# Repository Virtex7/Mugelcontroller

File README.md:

# Mugelcontroller
kleiner 12V-Umrichter für einen Secop-BD50 Kältekompressor

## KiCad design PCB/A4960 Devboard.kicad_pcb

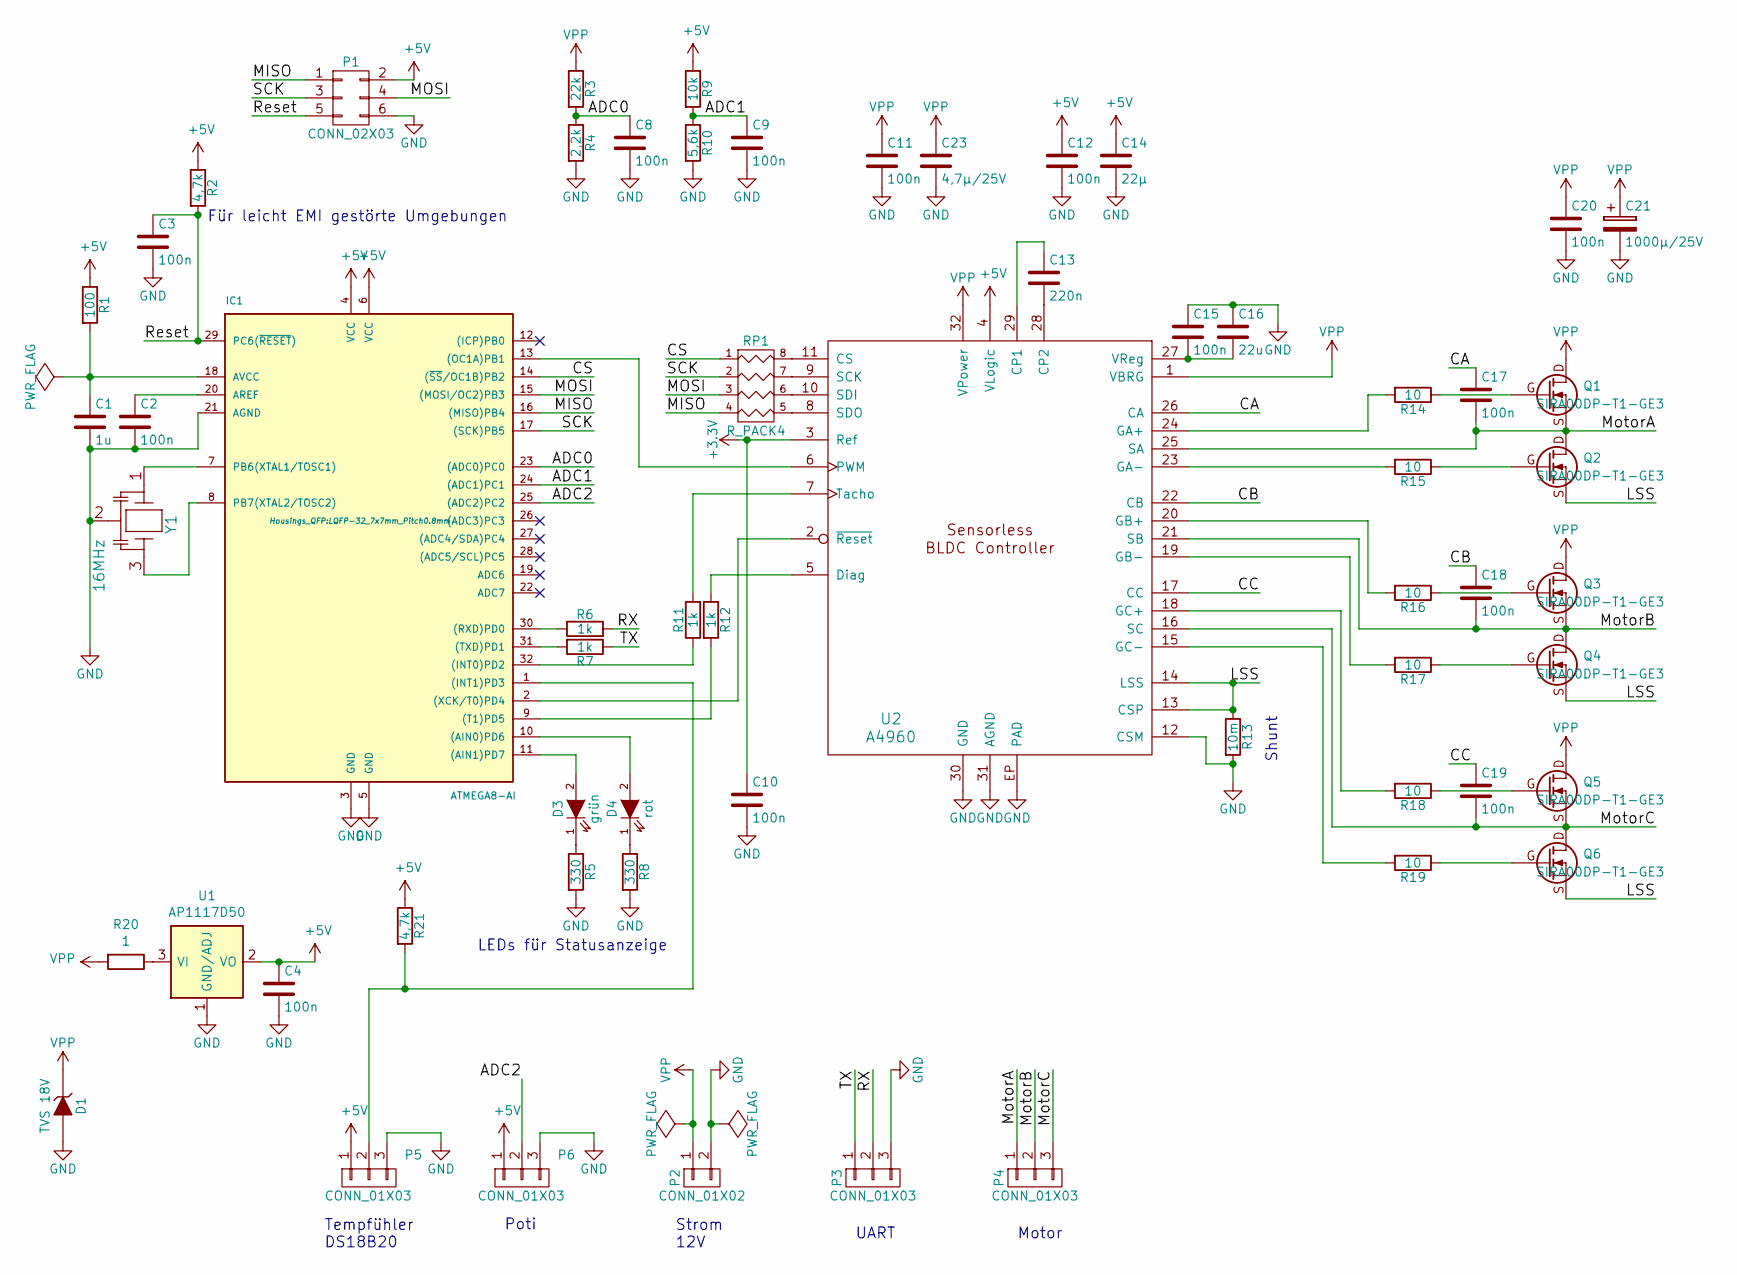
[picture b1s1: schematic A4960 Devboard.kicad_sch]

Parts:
C1: 1u; C_0603
C2, C3, C4, C8, C9, C10, C11, C12, C15, C17, C18, C19, C20: 100n; C_0603
C13: 220n; C_0603
C14: 22µ; C_1206
C16: 22u; C_1206
C21: 1000µ/25V; C_Radial_D8_L11.5_P3.5
C23: 4,7µ/25V; C_1206
D1: TVS 18V; SOD-123
D3: grün; LED-0603
D4: rot; LED-0603
IC1: ATMEGA8-AI; LQFP-32_7x7mm_Pitch0.8mm
P1: CONN_02X03; Pin_Header_Straight_2x03
P2: CONN_01X02; Pin_Header_Straight_1x02
P3, P4, P5, P6: CONN_01X03; Pin_Header_Straight_1x03
Q1, Q2, Q3, Q4, Q5, Q6: SIRA00DP-T1-GE3; SO8_WITH_Heatpipes_New
R1: 100; R_0603
R2, R21: 4,7k; R_0603
R3: 22k; R_0603
R4: 2,2k; R_0603
R5, R8: 330; R_0603
R6, R7, R11, R12: 1k; R_0603
R9: 10k; R_0603
R10: 5,6k; R_0603
R13: 10m; R_2512; Digikey-Nummer RHM.010AUCT-ND
R14, R15, R16, R17, R18, R19: 10; R_0603
R20: 1; R_0805
RP1: R_PACK4; R_Array_Concave_4x0603
U1: AP1117D50; SOT-223
U2: A4960; TQFP-32_7x7mm_Pitch0.8mm; Digikey-Nummer 620-1452-1-ND
Y1: 16MHz; CerOsc_3,2x1,3

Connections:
/ADC0: C8.1, IC1.23 ((ADC0)PC0), R3.2, R4.1
/ADC1: C9.1, IC1.24 ((ADC1)PC1), R9.2, R10.1
/CA: C17.1, U2.26 (CA)
/CB: C18.1, U2.22 (CB)
/CC: C19.1, U2.17 (CC)
/CS: IC1.14 ((~SS~/OC1B)PB2), RP1.1
/LSS: Q2.S, Q4.S, Q6.S, R13.1, U2.13 (CSP), U2.14 (LSS)
/MISO: IC1.16 ((MISO)PB4), P1.1, RP1.4
/MOSI: IC1.15 ((MOSI/OC2)PB3), P1.4, RP1.3
/MotorA: C17.2, P4.1, Q1.S, Q2.D, U2.25 (SA)
/MotorB: C18.2, P4.2, Q3.S, Q4.D, U2.21 (SB)
/MotorC: C19.2, P4.3, Q5.S, Q6.D, U2.16 (SC)
/RX: P3.2, R6.2
/Reset: C3.1, IC1.29 (PC6(~RESET~)), P1.5, R2.2
/SCK: IC1.17 ((SCK)PB5), P1.3, RP1.2
/TX: P3.1, R7.1
GND: C1.2, C2.2, C3.2, C4.2, C8.2, C9.2, C10.2, C11.2, C12.2, C14.2, C15.1, C16.1, C20.2, C21.2, C23.2, D1.2 (A), IC1.3 (GND), IC1.5 (GND), IC1.21 (AGND), P1.6, P2.2, P3.3, P5.3, P6.3, R4.2, R5.2, R8.2, R10.2, R13.2, U1.1 (GND/ADJ), U2.12 (CSM), U2.30 (GND), U2.31 (AGND), U2.EP (PAD), Y1.2
unnamed: C1.1, IC1.18 (AVCC), R1.2
unnamed: C2.1, IC1.20 (AREF)
unnamed: C13.1, U2.29 (CP1)
unnamed: C13.2, U2.28 (CP2)
unnamed: C15.2, C16.2, U2.27 (VReg)
unnamed: D3.1 (K), R5.1
unnamed: D3.2 (A), IC1.11 ((AIN1)PD7)
unnamed: D4.1 (K), R8.1
unnamed: D4.2 (A), IC1.10 ((AIN0)PD6)
unnamed: IC1.2 ((XCK/T0)PD4), U2.2 (~Reset)
unnamed: IC1.7 (PB6(XTAL1/TOSC1)), Y1.1
unnamed: IC1.8 (PB7(XTAL2/TOSC2)), Y1.3
unnamed: IC1.13 ((OC1A)PB1), U2.6 (PWM)
unnamed: IC1.25 ((ADC2)PC2), P6.2
unnamed: IC1.30 ((RXD)PD0), R6.1
unnamed: IC1.31 ((TXD)PD1), R7.2
unnamed: IC1.32 ((INT0)PD2), R11.1
unnamed: Q1.G, R14.1
unnamed: Q2.G, R15.1
unnamed: Q3.G, R16.1
unnamed: Q4.G, R17.1
unnamed: Q5.G, R18.1
unnamed: Q6.G, R19.1
unnamed: R11.2, U2.7 (Tacho)
unnamed: R12.1, U2.5 (Diag)
unnamed: R14.2, U2.24 (GA+)
unnamed: R15.2, U2.23 (GA-)
unnamed: R16.2, U2.20 (GB+)
unnamed: R17.2, U2.19 (GB-)
unnamed: R18.2, U2.18 (GC+)
unnamed: R19.2, U2.15 (GC-)
unnamed: R20.1, U1.3 (VI)
unnamed: RP1.5 (R4), U2.8 (SDO)
unnamed: RP1.6 (R3), U2.10 (SDI)
unnamed: RP1.7 (R2), U2.9 (SCK)
unnamed: RP1.8 (R1), U2.11 (CS)
VPP: C11.1, C20.1, C21.1, C23.1, D1.1 (K), P2.1, Q1.D, Q3.D, Q5.D, R3.1, R20.2, U2.1 (VBRG), U2.32 (VPower)

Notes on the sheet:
Für leicht EMI gestörte Umgebungen
Tempfühler DS18B20
LEDs für Statusanzeige
Poti
Strom 12V
UART
Motor
Shunt

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
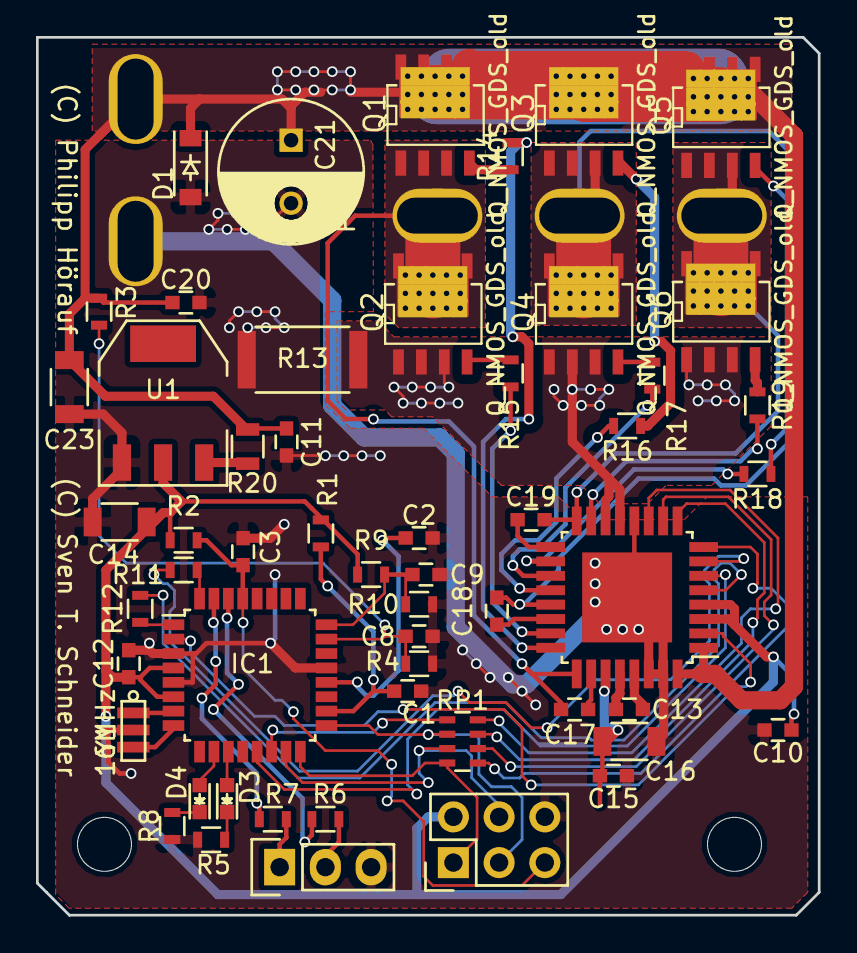
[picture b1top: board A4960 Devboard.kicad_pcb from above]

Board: 2 copper layers, 43.4 x 48.8 mm, 58 parts (0 on the bottom side), 55 nets.

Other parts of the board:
Mount: MountingHole_3mm
Mount#2: MountingHole_3mm

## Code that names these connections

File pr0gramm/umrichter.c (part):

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
volatile int8_t motorstatus = 0; // 0 heißt OFF, 1 RECHTS, -1 LINKS
void a4960Init (void) {
	sbi(PORTD, PD4); // aktiviere den a4960
	delayms(10);
	a4960Com (0b0001, BT3 | DT4 | DT2);
	a4960Com (0b0011, VR3 | VR2 | VR1 | VR0 | VT5);
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int main(void) {
	
	// Umrichteranschluss:
	// PB1/OC1A = PWM
	// PD2/INT0 = Tacho
	// PD3/INT1 = Diag
	// PD4 = Reset (active low)
	// SPI Daten über SPI, CS ist PB2
	DDRB |= 1<<PB1 | 1<<PB2 | 1<<PB3 | 1<<PB5;
	sbi(PORTD, PB5); // SCK ist active low
	
	// Sonstiges:
	// ADC0 = 
	// ADC1 = 
	// PD0/RXI = 
	// PD1/TXO = 
	DDRD |= 1<<PD1 | 1<<PD4;
	PORTD |= 1<<PD2 | 1<<PD3; // Pullups an
	
	// LEDs
	DDRD |= 1<<PD6 | 1<<PD7;
	
	delayms(10);
	
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
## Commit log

2015-09-07 Datenblätter von Controller und Orginal-Umrichter
2015-11-20 Library-Refferenz geändert & Layout: Vcc von 3.3V auf 5V
2015-11-23 PCB angefangen
2015-11-23 Änderung der FETs auf Pinnamen GDS
2015-11-26 PCB weiter
2015-11-26 V REF liegt nun auf 5V weil Datenblatt
2015-11-27 PCB weiter gemcht & neuer Spannungswandler auf 5V
2015-11-30 PCB fertig!
2015-11-30 Vcc-Fläche oben eingefügt.
2015-11-30 Mehr Vias!
2015-12-04 Bestückungsdruck und Befestigungsbohrungen
2015-12-04 Lötstopplack auf unterseite teilweise entfernt
2015-12-04 Q3 war nicht richtig angeschlossen...
2015-12-07 PowerPole-Stecker korrigiert
2015-12-07 Credits angegeben
2015-12-23 neue Datenblätter für den FU-Chip und das Target.
2015-12-23 Leiterplatte so gefertigt
2015-12-23 neue Endungen für Atmels Kompilier-Hilfsdateien dazugefügt
2015-12-24 Pr0gramm angefangen, Umrichter versucht anzulaufen. aufspaltung in umrichter.h und umrichter.c, damit Ordnung herrscht.
2015-12-26 Schaltplan: fehlende Bauteilwerte eingetragen Programm: Motor läuft an. jetzt fehlen noch Regelung und diverse ADC/Timer-Auswertungen
2015-12-26 float-printf aktiviert, achtung, speicherverbrauch!
2015-12-26 kleiner PI-regler, noch mit fester Frequenz, eingebaut
2015-12-27 PI Regler leicht angepasst, dazu eine Steuermöglichkeit über die Konsole integriert, x stoppt den Motor nun sofort.
2016-02-20 fehlende zwei Anschlüsse hinzugefügt.
2016-02-20 Pullup für DS18B20 Tempsensor hinzugefügt.
2016-04-12 Neue Bauteile eingefügt und angeschlossen
2016-04-15 Vref auf 5V gelegt und PCB fertig gelayoutet
2021-04-11 Experimenteller UART
    Uart interface jetzt wie folgt:
    Motor start <s>
    Motor stop <x>
    Motor rückwärts <z>
    Motor RPM <r500r3> erste zahl: RPM, zweite Zahl: anzahl der stellen der RPM
2021-04-12 Nachrichten angepasst
2021-04-13 last commit des "alten" Standes von 2016
2021-04-13 neue KiCAD Dateien ohne BACKUPS hinzugefügt
2021-04-13 Interface für die Verstellung von Ki und Kp hinzugefügt.

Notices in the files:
pr0gramm/umrichter.c:
License: GPLv3 or later
Author: Copyright (C) Philipp Hörauf
This program is free software; you can redistribute it and/or modify
it under the terms of the GNU General Public License as published by
the Free Software Foundation; either version 2 of the License, or
(at your option) any later version.
